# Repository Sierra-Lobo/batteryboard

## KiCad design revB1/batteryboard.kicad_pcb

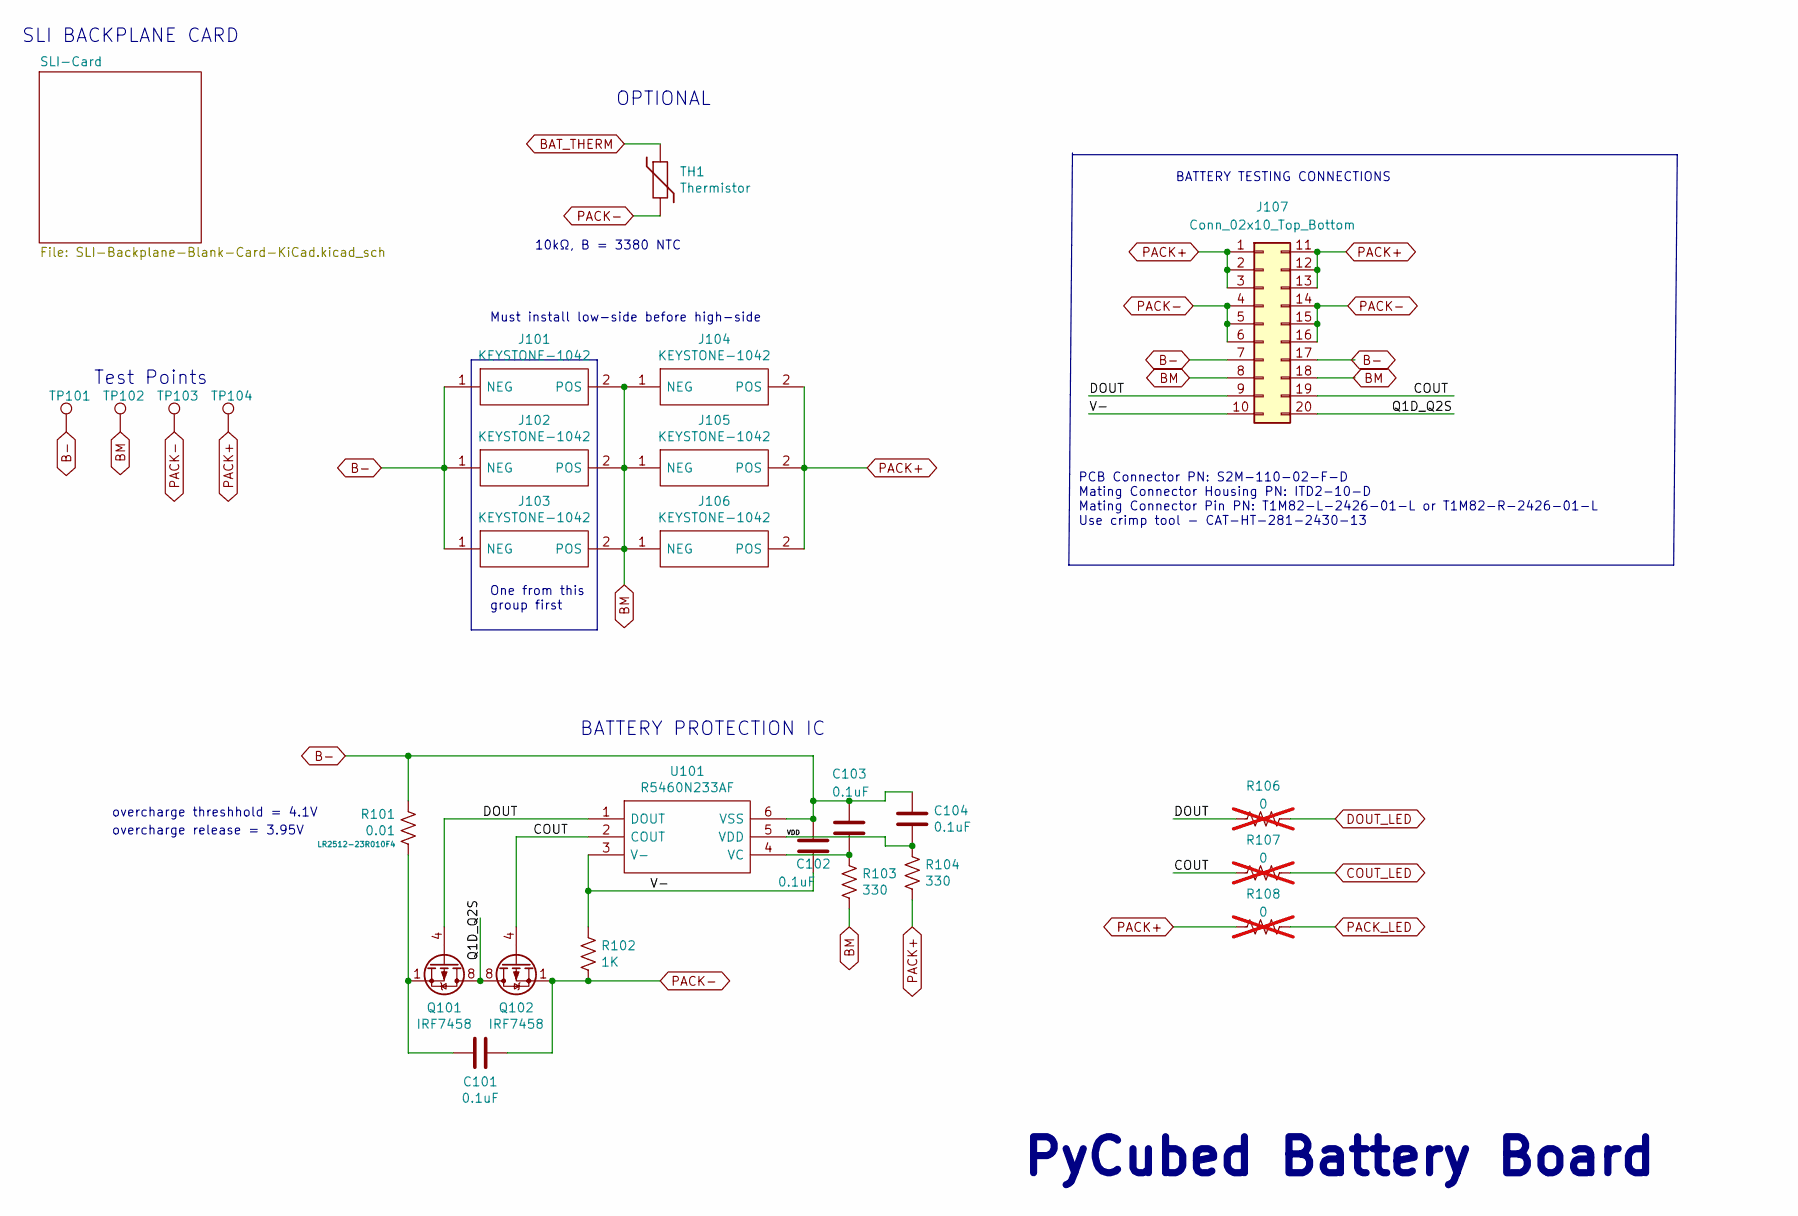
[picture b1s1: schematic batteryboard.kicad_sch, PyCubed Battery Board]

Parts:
C101, C102, C103, C104: 0.1uF; C_0603_1608Metric
J101: KEYSTONE-1042; KEYSTONE-1042_ALT_J1; Manufacturer_Part_Number 1042; Mouser Part Number 534-1042
J102, J104, J106: KEYSTONE-1042; Manufacturer_Part_Number 1042; Mouser Part Number 534-1042
J103: KEYSTONE-1042; KEYSTONE-1042_ALT_J5; Manufacturer_Part_Number 1042; Mouser Part Number 534-1042
J105: KEYSTONE-1042; KEYSTONE-1042_alt_J4; Manufacturer_Part_Number 1042; Mouser Part Number 534-1042
J107: Conn_02x10_Top_Bottom; SAMTEC_S2M-110-02-X-D
Q101, Q102: IRF7458; SOIC-8_3.9x4.9mm_P1.27mm; Manufacturer_Part_Number IRF7458
R101: 0.01; R_2512_6332Metric
R102: 1K; R_0603_1608Metric; Manufacturer_Part_Number LR2512-23R010F4
R103, R104: 330; R_0603_1608Metric
R106, R107, R108: 0; R_0603_1608Metric; not fitted
TH1: Thermistor; R_Axial_DIN0204_L3.6mm_D1.6mm_P5.08mm_Vertical
TP101, TP102, TP103, TP104: TestPoint; TestPoint_Loop_D1.80mm_Drill1.0mm_Beaded
U101: R5460N233AF; SOT95P280X130-6N; Manufacturer_Part_Number R5460N233AF-TR-FE; Mouser Part Number 848-R5460N233AFTRFE

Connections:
/COUT: J107.19, Q102.4 (G), R107.2, U101.2 (COUT)
/DOUT: J107.9, Q101.4 (G), R106.2, U101.1 (DOUT)
/Q1D_Q2S: J107.20, Q101.5 (D), Q101.6 (D), Q101.7 (D), Q101.8 (D), Q102.5 (D), Q102.6 (D), Q102.7 (D), Q102.8 (D)
/V-: C102.2, J107.10, R102.1, U101.3 (V-)
/VDD: C104.2, R104.2, U101.5 (VDD)
B-: C102.1, C103.1, C104.1, J101.1 (NEG), J102.1 (NEG), J103.1 (NEG), J107.7, J107.17, R101.1, TP101.1, U101.6 (VSS)
BAT_THERM: TH1.1; also elsewhere on the board
BM: J101.2 (POS), J102.2 (POS), J103.2 (POS), J104.1 (NEG), J105.1 (NEG), J106.1 (NEG), J107.8, J107.18, R103.1, TP102.1
COUT_LED: R107.1; also elsewhere on the board
DOUT_LED: R106.1; also elsewhere on the board
unnamed: C101.1, Q101.1 (S), Q101.2 (S), Q101.3 (S), R101.2
unnamed: C103.2, R103.2, U101.4 (VC)
PACK+: J104.2 (POS), J105.2 (POS), J106.2 (POS), J107.1, J107.2, J107.3, J107.11, J107.12, J107.13, R104.1, R108.2, TP104.1; also elsewhere on the board
PACK-: C101.2, J107.4, J107.5, J107.6, J107.14, J107.15, J107.16, Q102.1 (S), Q102.2 (S), Q102.3 (S), R102.2, TH1.2, TP103.1; also elsewhere on the board
PACK_LED: R108.1; also elsewhere on the board

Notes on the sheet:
overcharge release = 3.95V
Test Points
PCB Connector PN: S2M-110-02-F-D Mating Connector Housing PN: ITD2-10-D Mating Connector Pin PN: T1M82-L-2426-01-L or T1M82-R-2426-01-L Use crimp tool - CAT-HT-281-2430-13
Must install low-side before high-side
SLI BACKPLANE CARD
BATTERY TESTING CONNECTIONS
overcharge threshhold = 4.1V
OPTIONAL
BATTERY PROTECTION IC
One from this group first
PyCubed Battery Board
10kΩ, B = 3380 NTC

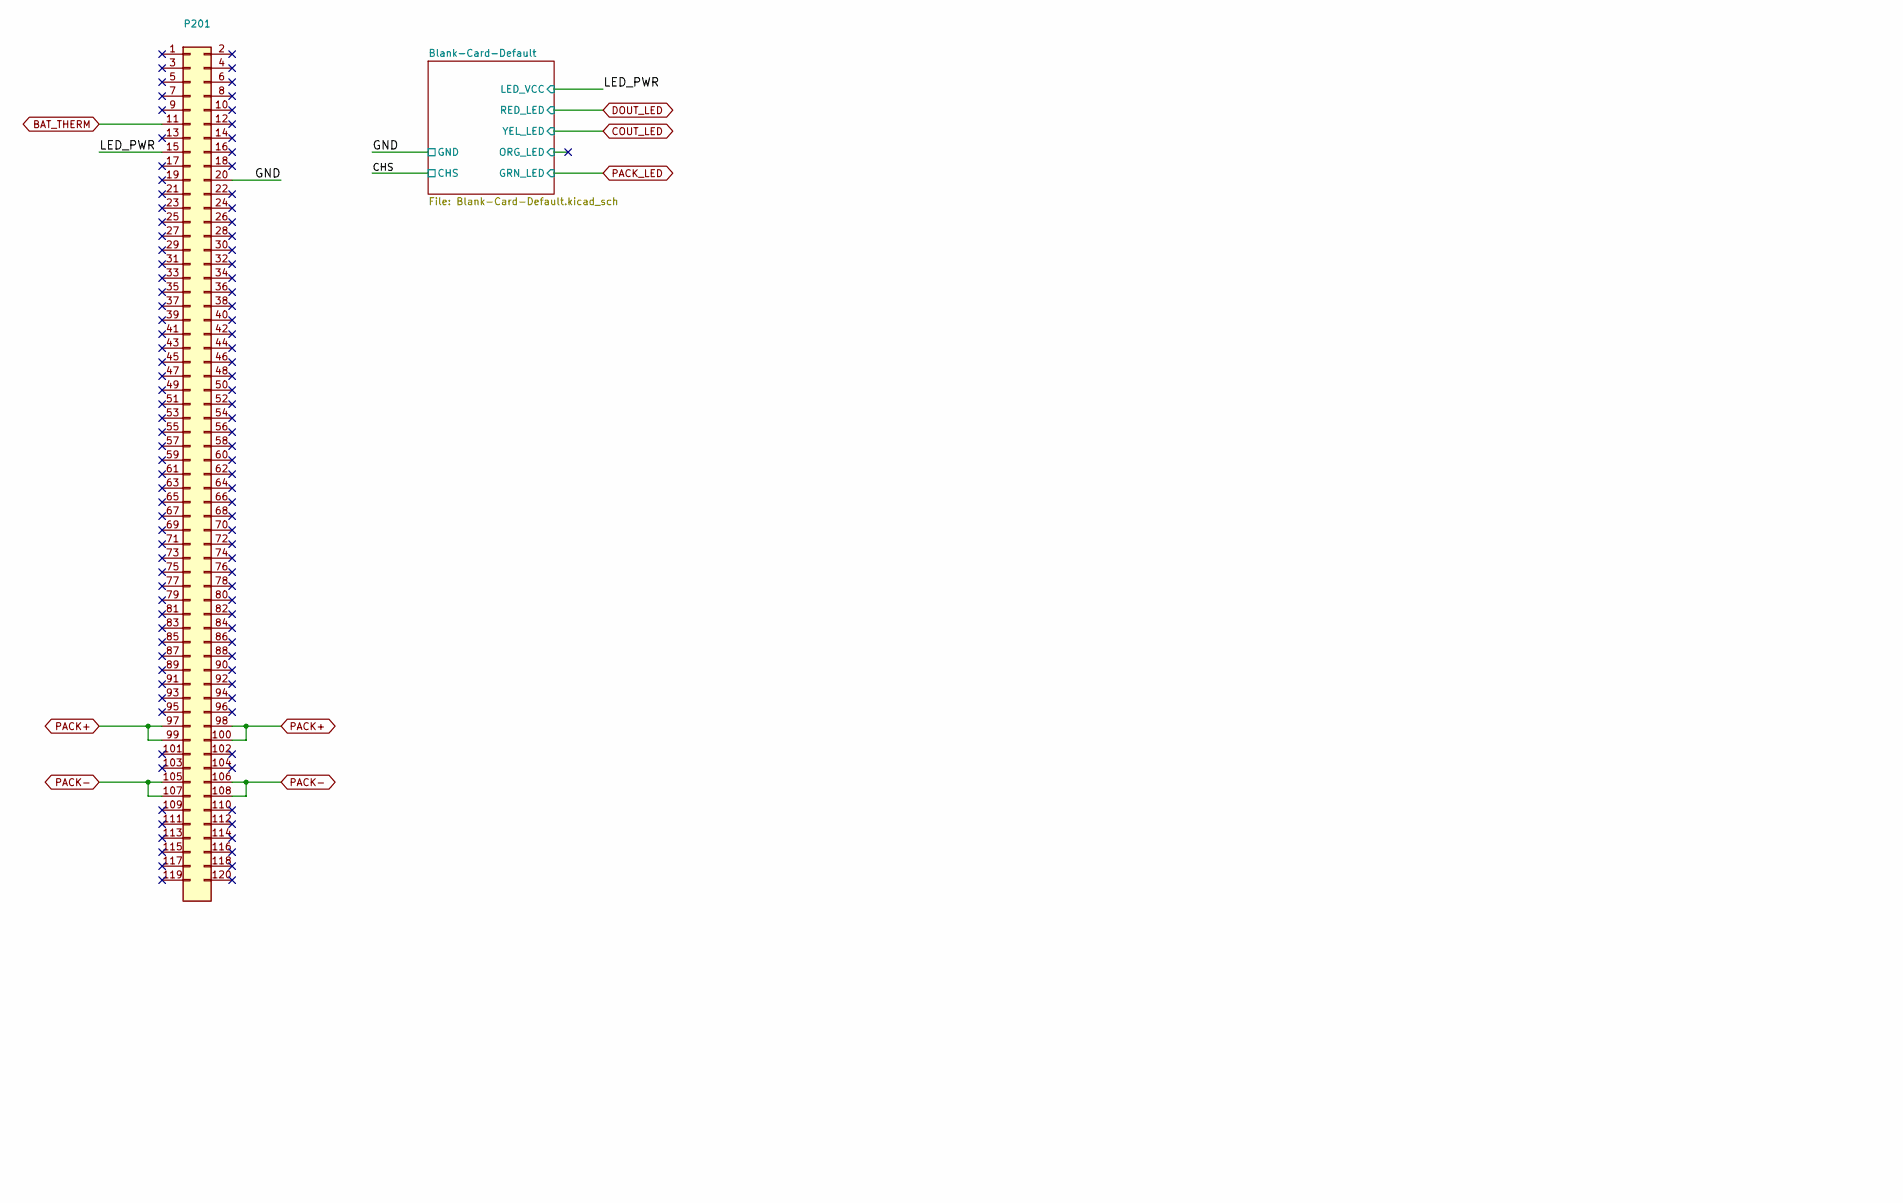
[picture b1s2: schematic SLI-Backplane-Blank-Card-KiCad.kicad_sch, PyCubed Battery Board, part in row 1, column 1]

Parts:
P201: Conn_02x60_Top_Bottom; HSEC8-160-CARD-EDGE

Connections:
/SLI-Card/GND: P201.20; also elsewhere on the board
/SLI-Card/LED_PWR: P201.15; also elsewhere on the board
BAT_THERM: P201.11; also elsewhere on the board
PACK+: P201.97, P201.98, P201.99, P201.100; also elsewhere on the board
PACK-: P201.105, P201.106, P201.107, P201.108; also elsewhere on the board

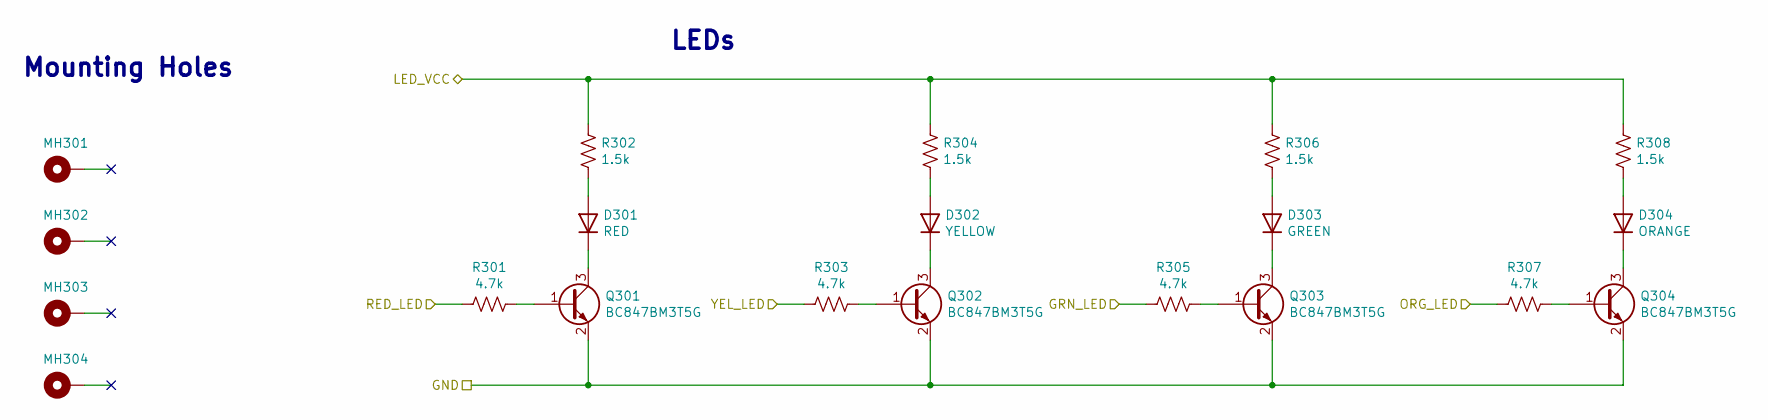
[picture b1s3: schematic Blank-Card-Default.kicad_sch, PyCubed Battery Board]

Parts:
D301: RED; APA2107x; Manufacturer_Part_Number APA2107LSECK/J3-PRV
D302: YELLOW; APA2107x; Manufacturer_Part_Number APA2107SYCK/J3-PRV
D303: GREEN; APA2107x; Manufacturer_Part_Number APA2107CGCK
D304: ORANGE; APA2107x; Manufacturer_Part_Number APA2107SECK/J4-PRV
MH301: MountingHole_Pad; 125mil_hole
MH302, MH303, MH304: SLI-Backplane-Blank-Card-KiCad:125mil_hole; 125mil_hole
Q301, Q302, Q303, Q304: BC847BM3T5G; SOT-723; Manufacturer_Part_Number BC847BM3T5G
R301, R303, R305, R307: 4.7k; R_0402_1005Metric
R302, R304, R306, R308: 1.5k; R_0402_1005Metric

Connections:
/SLI-Card/Blank-Card-Default/ORG_LED: R307.2
/SLI-Card/GND: Q301.2 (E), Q302.2 (E), Q303.2 (E), Q304.2 (E); also elsewhere on the board
/SLI-Card/LED_PWR: R302.1, R304.1, R306.1, R308.1; also elsewhere on the board
COUT_LED: R303.2; also elsewhere on the board
DOUT_LED: R301.2; also elsewhere on the board
unnamed: D301.2 (A), R302.2
unnamed: D301.1 (K), Q301.3 (C)
unnamed: D302.2 (A), R304.2
unnamed: D302.1 (K), Q302.3 (C)
unnamed: D303.2 (A), R306.2
unnamed: D303.1 (K), Q303.3 (C)
unnamed: D304.2 (A), R308.2
unnamed: D304.1 (K), Q304.3 (C)
unnamed: Q301.1 (B), R301.1
unnamed: Q302.1 (B), R303.1
unnamed: Q303.1 (B), R305.1
unnamed: Q304.1 (B), R307.1
PACK_LED: R305.2; also elsewhere on the board

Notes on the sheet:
Mounting Holes
LEDs

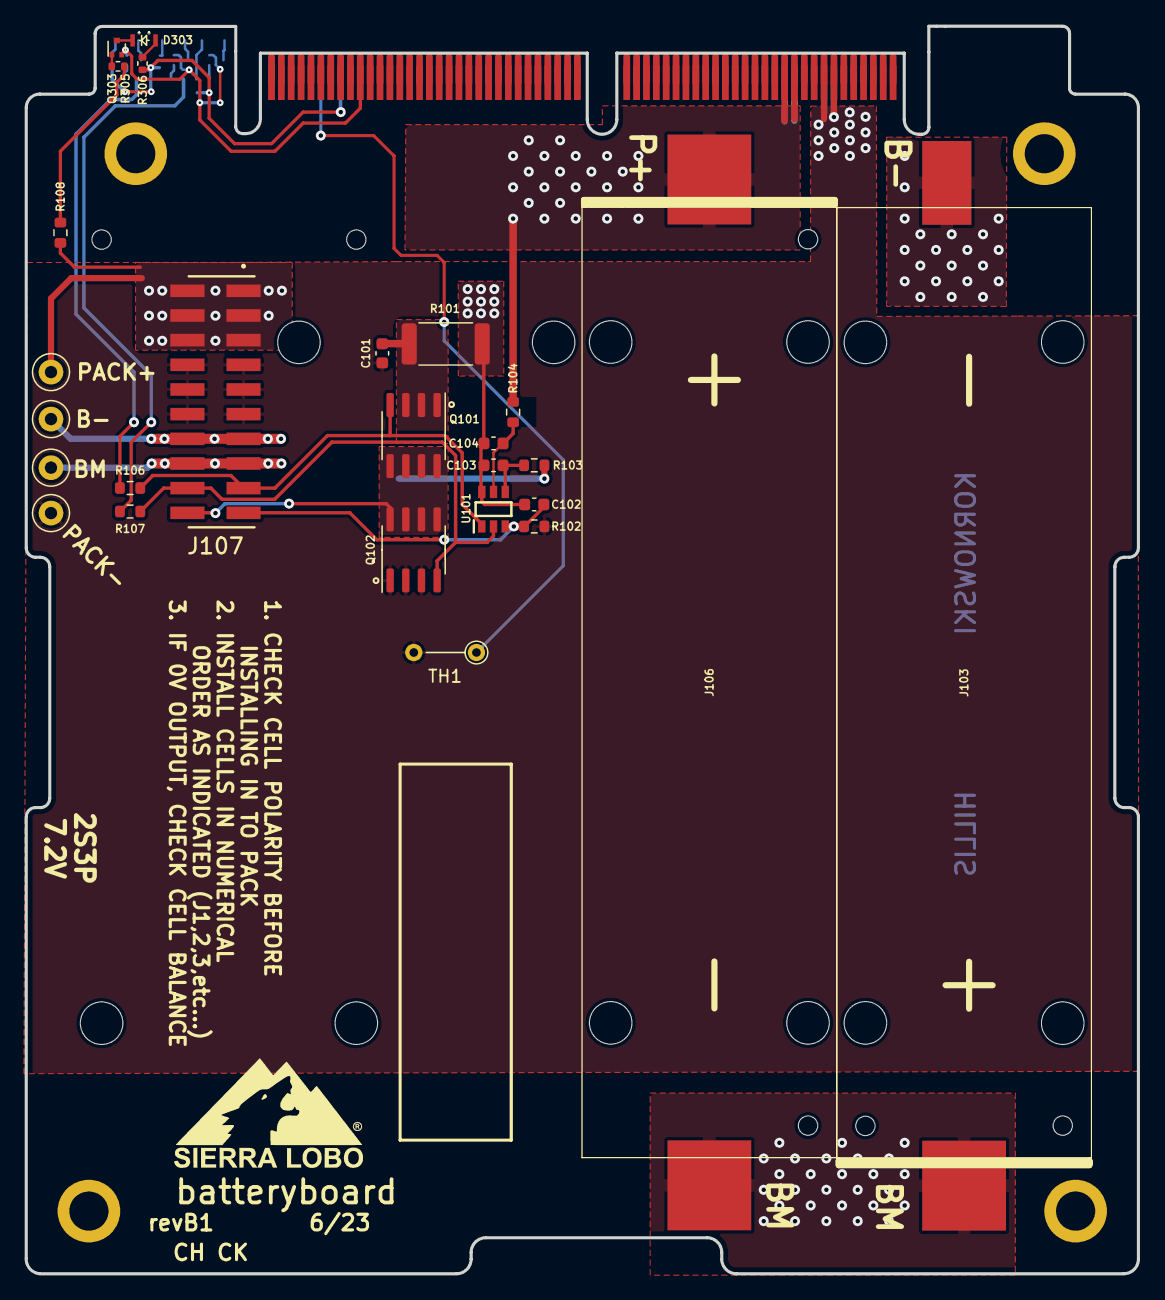
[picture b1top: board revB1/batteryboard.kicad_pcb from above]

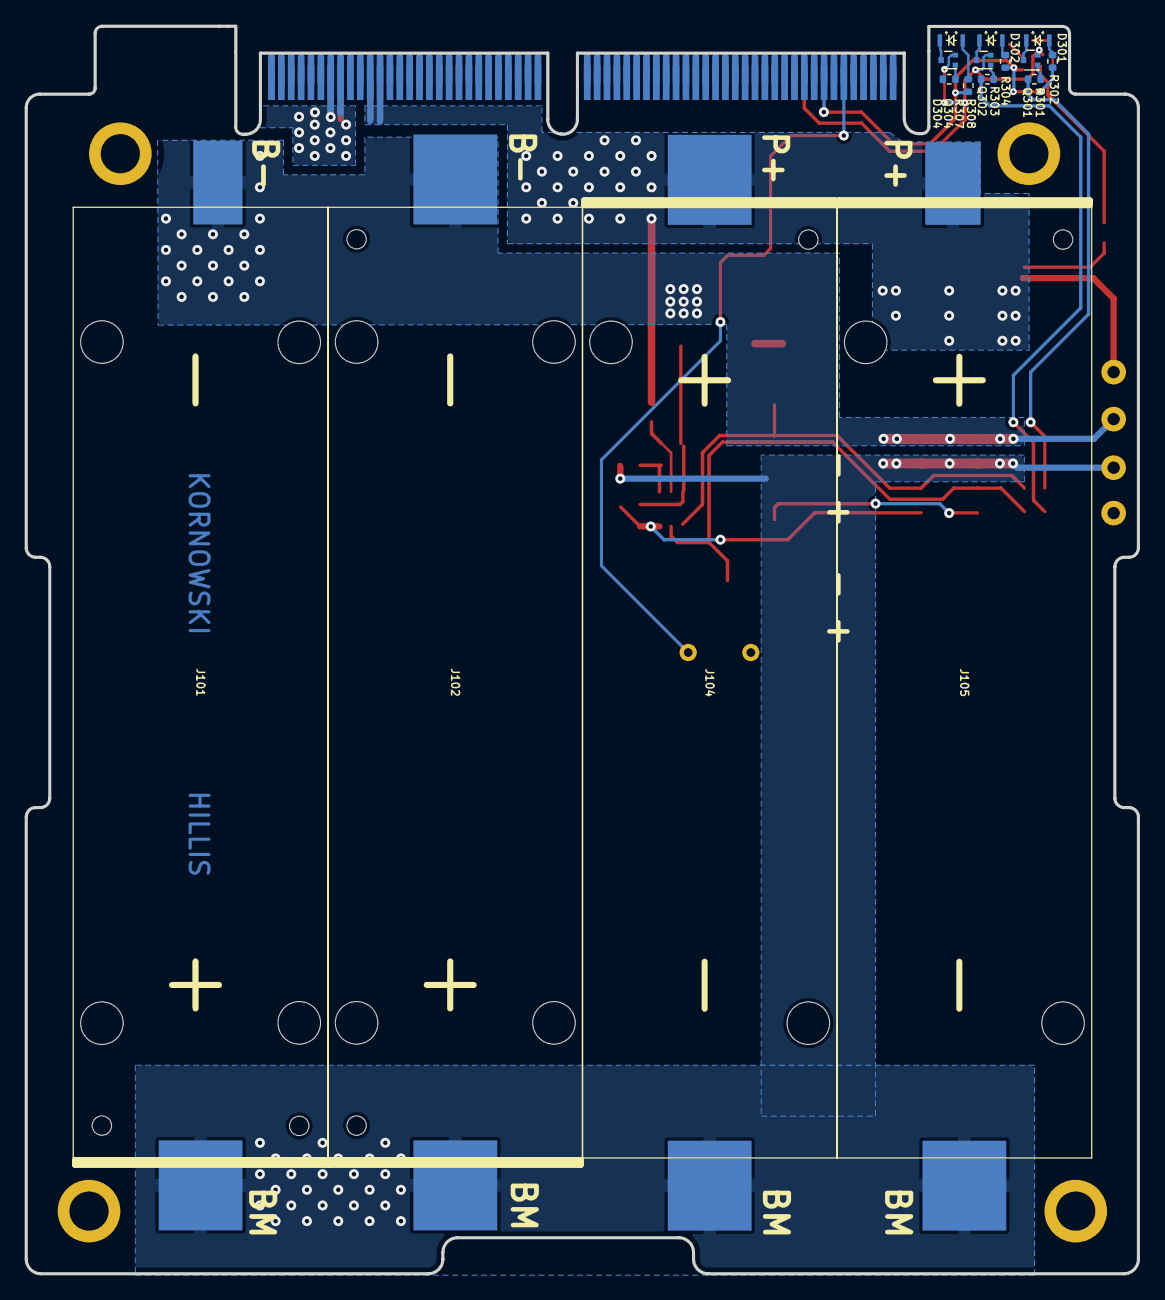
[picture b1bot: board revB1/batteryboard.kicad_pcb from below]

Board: 2 copper layers, 90.2 x 101.1 mm, 47 parts (16 on the bottom side), 29 nets.

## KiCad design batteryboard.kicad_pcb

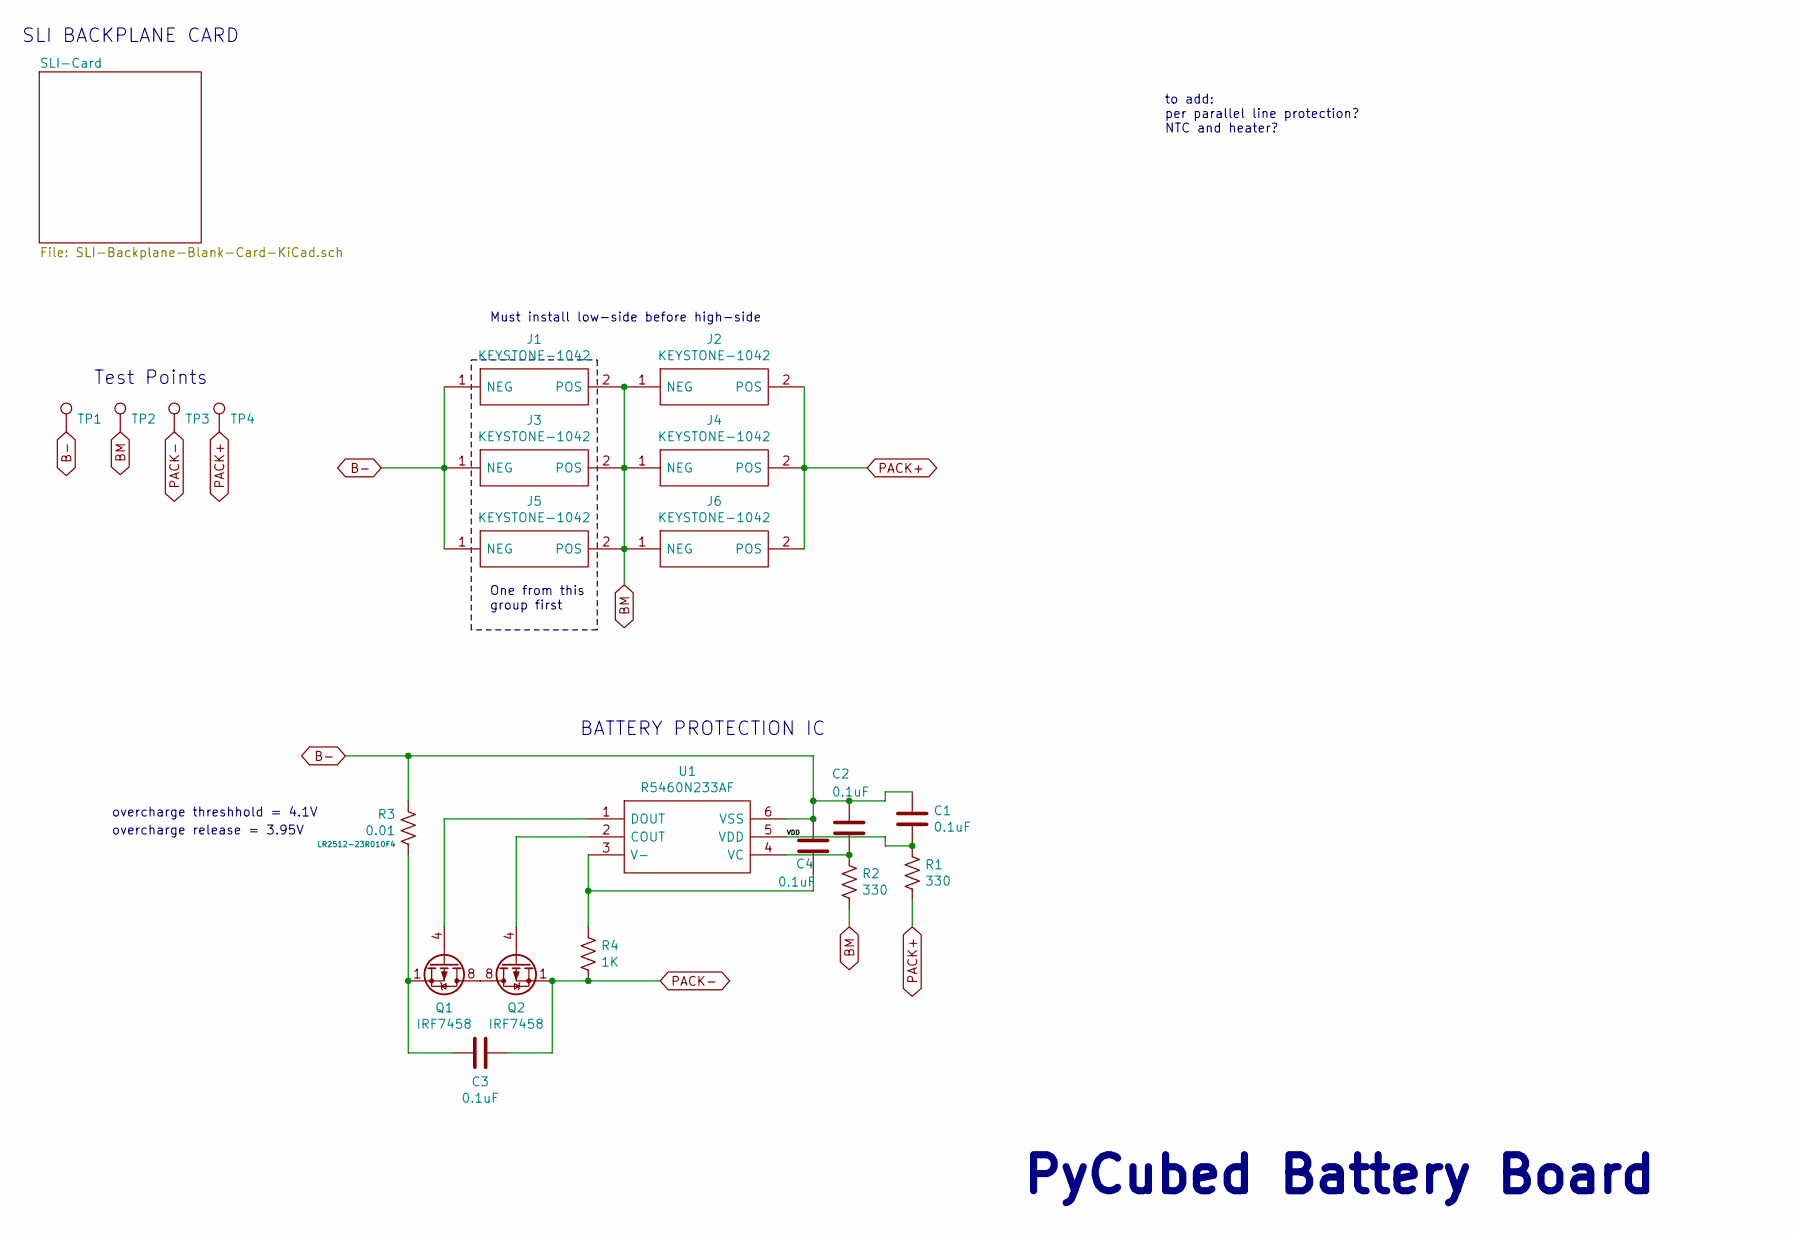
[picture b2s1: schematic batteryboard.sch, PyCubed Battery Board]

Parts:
C1, C2, C3, C4: 0.1uF; C_0603_1608Metric
J1: KEYSTONE-1042; KEYSTONE-1042_ALT_J1; Manufacturer_Part_Number 1042; Mouser Part Number 534-1042
J2, J3, J6: KEYSTONE-1042; Manufacturer_Part_Number 1042; Mouser Part Number 534-1042
J4: KEYSTONE-1042; KEYSTONE-1042_alt_J4; Manufacturer_Part_Number 1042; Mouser Part Number 534-1042
J5: KEYSTONE-1042; KEYSTONE-1042_ALT_J5; Manufacturer_Part_Number 1042; Mouser Part Number 534-1042
Q1, Q2: IRF7458; SOIC-8_3.9x4.9mm_P1.27mm; Manufacturer_Part_Number IRF7458
R1, R2: 330; R_0603_1608Metric
R3: 0.01; R_2512_6332Metric
R4: 1K; R_0603_1608Metric; Manufacturer_Part_Number LR2512-23R010F4
TP1, TP2, TP3, TP4: TestPoint; TestPoint_Loop_D1.80mm_Drill1.0mm_Beaded
U1: R5460N233AF; SOT95P280X130-6N; Manufacturer_Part_Number R5460N233AF-TR-FE; Mouser Part Number 848-R5460N233AFTRFE

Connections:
/VDD: C1.2, R1.2, U1.5 (VDD)
B-: C1.1, C2.1, C4.1, J1.1 (NEG), J3.1 (NEG), J5.1 (NEG), R3.1, TP1.1, U1.6 (VSS)
BM: J1.2 (POS), J2.1 (NEG), J3.2 (POS), J4.1 (NEG), J5.2 (POS), J6.1 (NEG), R2.1, TP2.1
unnamed: C2.2, R2.2, U1.4 (VC)
unnamed: C3.1, Q1.1 (S), Q1.2 (S), Q1.3 (S), R3.2
unnamed: C4.2, R4.1, U1.3 (V-)
unnamed: Q1.4 (G), U1.1 (DOUT)
unnamed: Q1.5 (D), Q1.6 (D), Q1.7 (D), Q1.8 (D), Q2.5 (D), Q2.6 (D), Q2.7 (D), Q2.8 (D)
unnamed: Q2.4 (G), U1.2 (COUT)
PACK+: J2.2 (POS), J4.2 (POS), J6.2 (POS), R1.1, TP4.1; also elsewhere on the board
PACK-: C3.2, Q2.1 (S), Q2.2 (S), Q2.3 (S), R4.2, TP3.1; also elsewhere on the board

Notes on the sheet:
Must install low-side before high-side
One from this group first
Test Points
BATTERY PROTECTION IC
PyCubed Battery Board
SLI BACKPLANE CARD
overcharge threshhold = 4.1V
overcharge release = 3.95V
to add: per parallel line protection? NTC and heater?

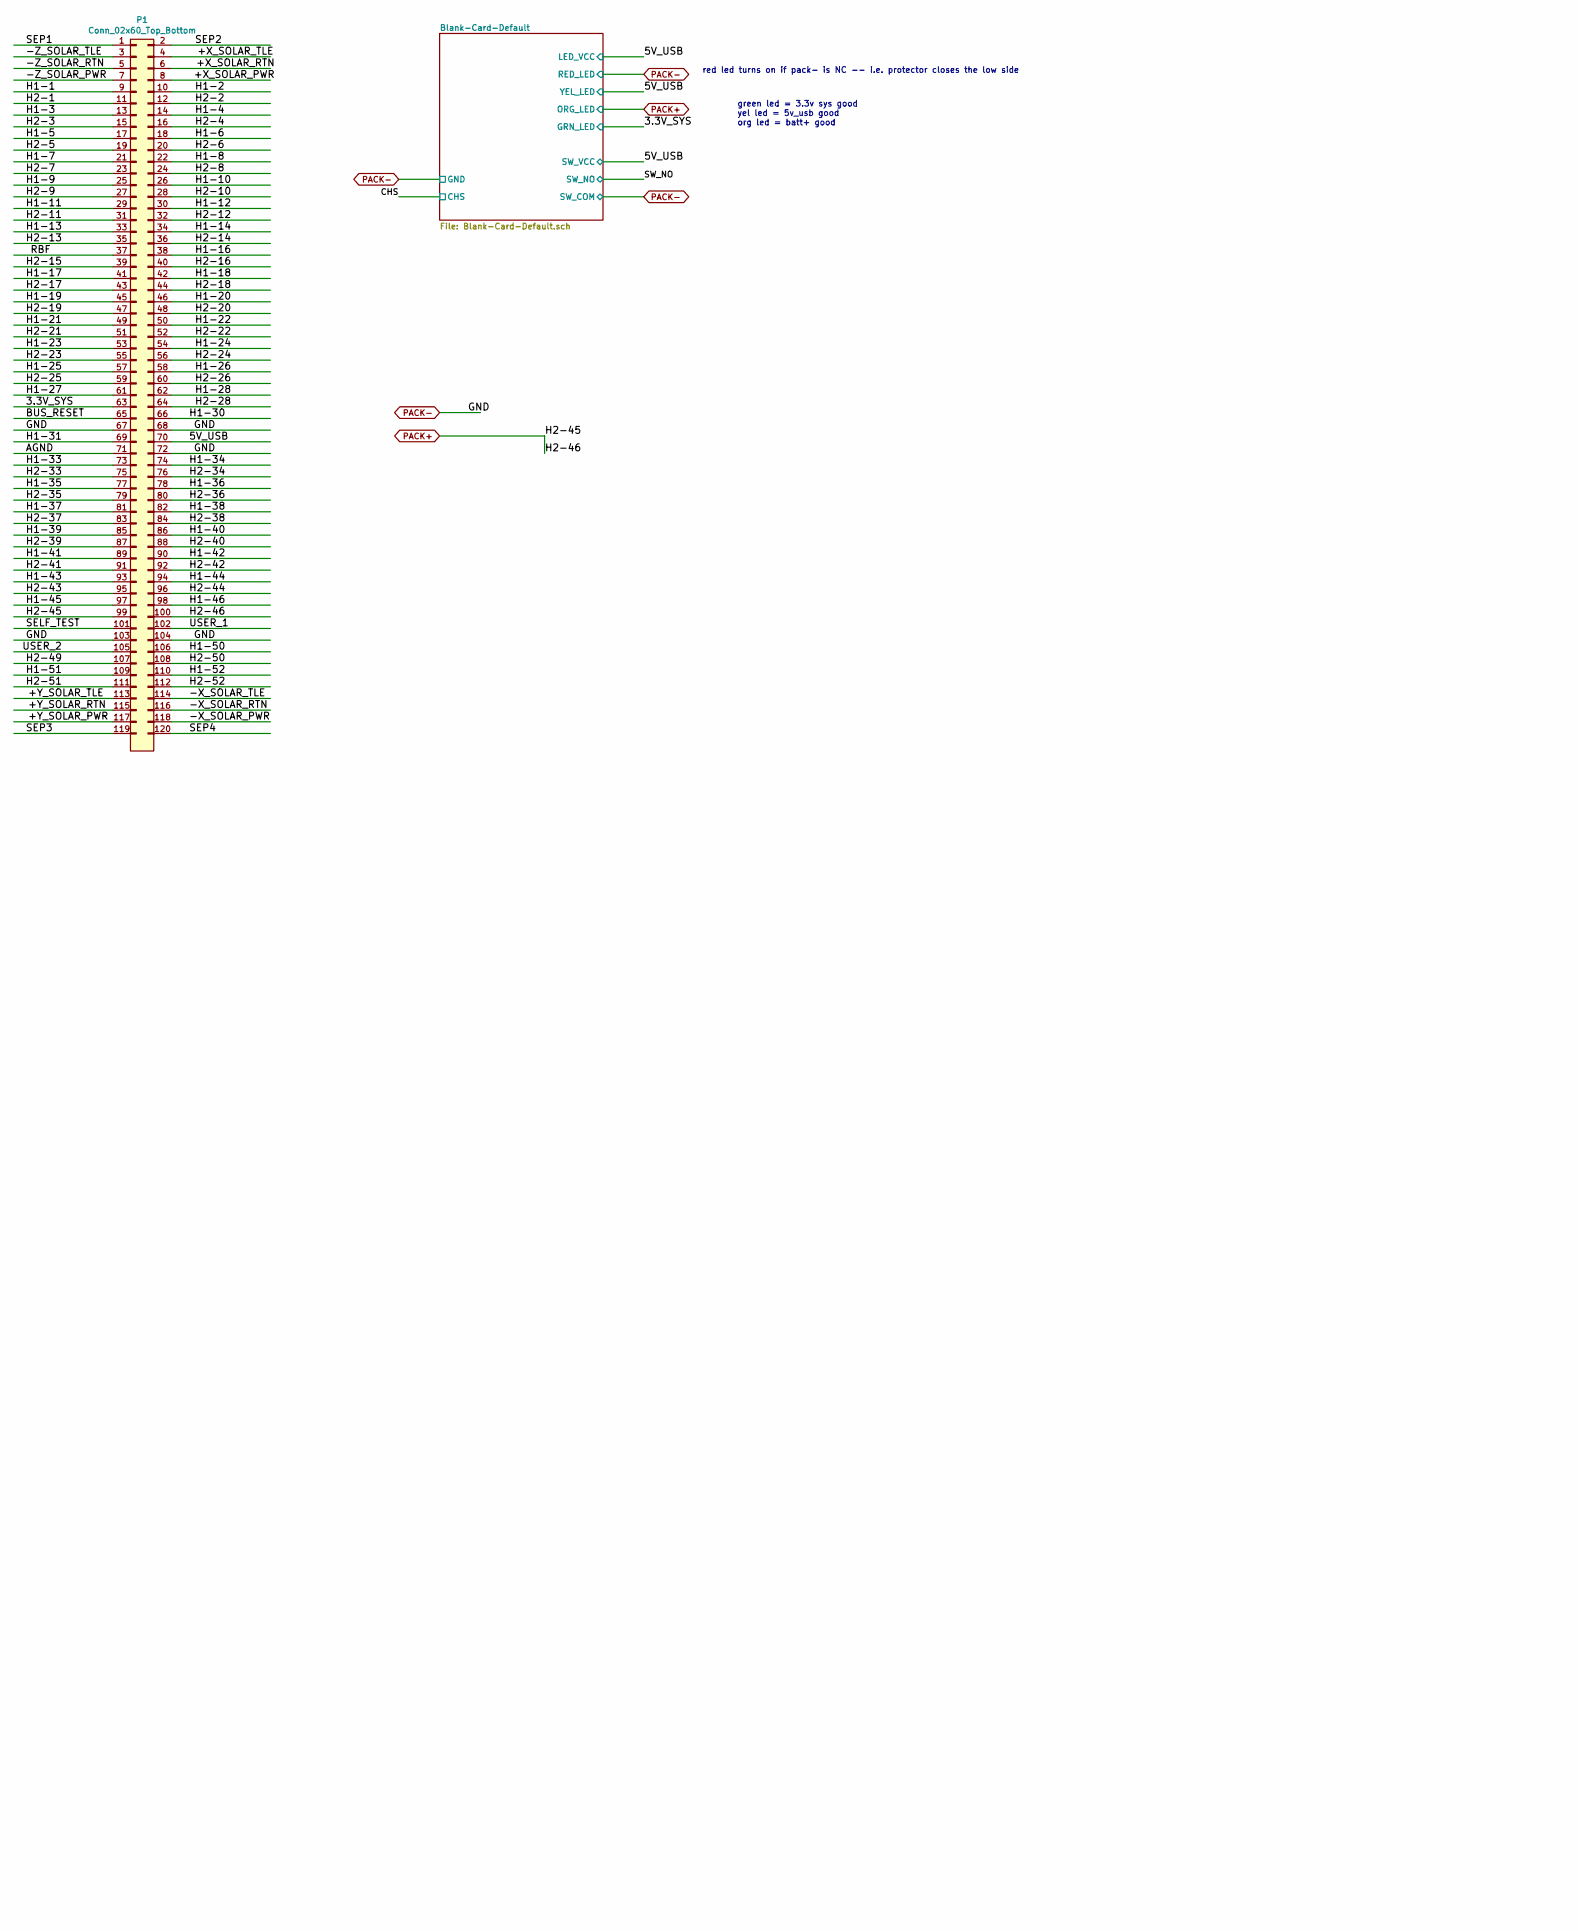
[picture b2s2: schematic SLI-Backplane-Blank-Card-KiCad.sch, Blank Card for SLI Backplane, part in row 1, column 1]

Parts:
P1: Conn_02x60_Top_Bottom; HSEC8-160-CARD-EDGE

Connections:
/SLI-Card/3.3V_SYS: P1.63; also elsewhere on the board
/SLI-Card/5V_USB: P1.70; also elsewhere on the board
/SLI-Card/+X_SOLAR_PWR: P1.8
/SLI-Card/+X_SOLAR_RTN: P1.6
/SLI-Card/+X_SOLAR_TLE: P1.4
/SLI-Card/+Y_SOLAR_PWR: P1.117
/SLI-Card/+Y_SOLAR_RTN: P1.115
/SLI-Card/+Y_SOLAR_TLE: P1.113
/SLI-Card/-X_SOLAR_PWR: P1.118
/SLI-Card/-X_SOLAR_RTN: P1.116
/SLI-Card/-X_SOLAR_TLE: P1.114
/SLI-Card/-Z_SOLAR_PWR: P1.7
/SLI-Card/-Z_SOLAR_RTN: P1.5
/SLI-Card/-Z_SOLAR_TLE: P1.3
/SLI-Card/AGND: P1.71
/SLI-Card/BUS_RESET: P1.65
/SLI-Card/H1-1: P1.9
/SLI-Card/H1-2: P1.10
/SLI-Card/H1-3: P1.13
/SLI-Card/H1-4: P1.14
/SLI-Card/H1-5: P1.17
/SLI-Card/H1-6: P1.18
/SLI-Card/H1-7: P1.21
/SLI-Card/H1-8: P1.22
/SLI-Card/H1-9: P1.25
/SLI-Card/H1-10: P1.26
/SLI-Card/H1-11: P1.29
/SLI-Card/H1-12: P1.30
/SLI-Card/H1-13: P1.33
/SLI-Card/H1-14: P1.34
/SLI-Card/H1-16: P1.38
/SLI-Card/H1-17: P1.41
/SLI-Card/H1-18: P1.42
/SLI-Card/H1-19: P1.45
/SLI-Card/H1-20: P1.46
/SLI-Card/H1-21: P1.49
/SLI-Card/H1-22: P1.50
/SLI-Card/H1-23: P1.53
/SLI-Card/H1-24: P1.54
/SLI-Card/H1-25: P1.57
/SLI-Card/H1-26: P1.58
/SLI-Card/H1-27: P1.61
/SLI-Card/H1-28: P1.62
/SLI-Card/H1-30: P1.66
/SLI-Card/H1-31: P1.69
/SLI-Card/H1-33: P1.73
/SLI-Card/H1-34: P1.74
/SLI-Card/H1-35: P1.77
/SLI-Card/H1-36: P1.78
/SLI-Card/H1-37: P1.81
/SLI-Card/H1-38: P1.82
/SLI-Card/H1-39: P1.85
/SLI-Card/H1-40: P1.86
/SLI-Card/H1-41: P1.89
/SLI-Card/H1-42: P1.90
/SLI-Card/H1-43: P1.93 (Pin93)
/SLI-Card/H1-44: P1.94
/SLI-Card/H1-45: P1.97
/SLI-Card/H1-46: P1.98
/SLI-Card/H1-50: P1.106
/SLI-Card/H1-51: P1.109
/SLI-Card/H1-52: P1.110
/SLI-Card/H2-1: P1.11
/SLI-Card/H2-2: P1.12
/SLI-Card/H2-3: P1.15
/SLI-Card/H2-4: P1.16
/SLI-Card/H2-5: P1.19
/SLI-Card/H2-6: P1.20
/SLI-Card/H2-7: P1.23
/SLI-Card/H2-8: P1.24
/SLI-Card/H2-9: P1.27
/SLI-Card/H2-10: P1.28
/SLI-Card/H2-11: P1.31
/SLI-Card/H2-12: P1.32
/SLI-Card/H2-13: P1.35
/SLI-Card/H2-14: P1.36
/SLI-Card/H2-15: P1.39
/SLI-Card/H2-16: P1.40
/SLI-Card/H2-17: P1.43
/SLI-Card/H2-18: P1.44
/SLI-Card/H2-19: P1.47
/SLI-Card/H2-20: P1.48
/SLI-Card/H2-21: P1.51
/SLI-Card/H2-22: P1.52
/SLI-Card/H2-23: P1.55
/SLI-Card/H2-24: P1.56
/SLI-Card/H2-25: P1.59
/SLI-Card/H2-26: P1.60
/SLI-Card/H2-28: P1.64
/SLI-Card/H2-33: P1.75
/SLI-Card/H2-34: P1.76
/SLI-Card/H2-35: P1.79
/SLI-Card/H2-36: P1.80
/SLI-Card/H2-37: P1.83
/SLI-Card/H2-38: P1.84
/SLI-Card/H2-39: P1.87
/SLI-Card/H2-40: P1.88
/SLI-Card/H2-41: P1.91
/SLI-Card/H2-42: P1.92
/SLI-Card/H2-43: P1.95
/SLI-Card/H2-44: P1.96
/SLI-Card/H2-49: P1.107
/SLI-Card/H2-50: P1.108
/SLI-Card/H2-51: P1.111
/SLI-Card/H2-52: P1.112
/SLI-Card/RBF: P1.37
/SLI-Card/SELF_TEST: P1.101
/SLI-Card/SEP1: P1.1
/SLI-Card/SEP2: P1.2
/SLI-Card/SEP3: P1.119
/SLI-Card/SEP4: P1.120
/SLI-Card/USER_1: P1.102
/SLI-Card/USER_2: P1.105
PACK+: P1.99, P1.100; also elsewhere on the board
PACK-: P1.67, P1.68, P1.72, P1.103, P1.104; also elsewhere on the board

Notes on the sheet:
green led = 3.3v sys good yel led = 5v_usb good org led = batt+ good
red led turns on if pack- is NC -- i.e. protector closes the low side

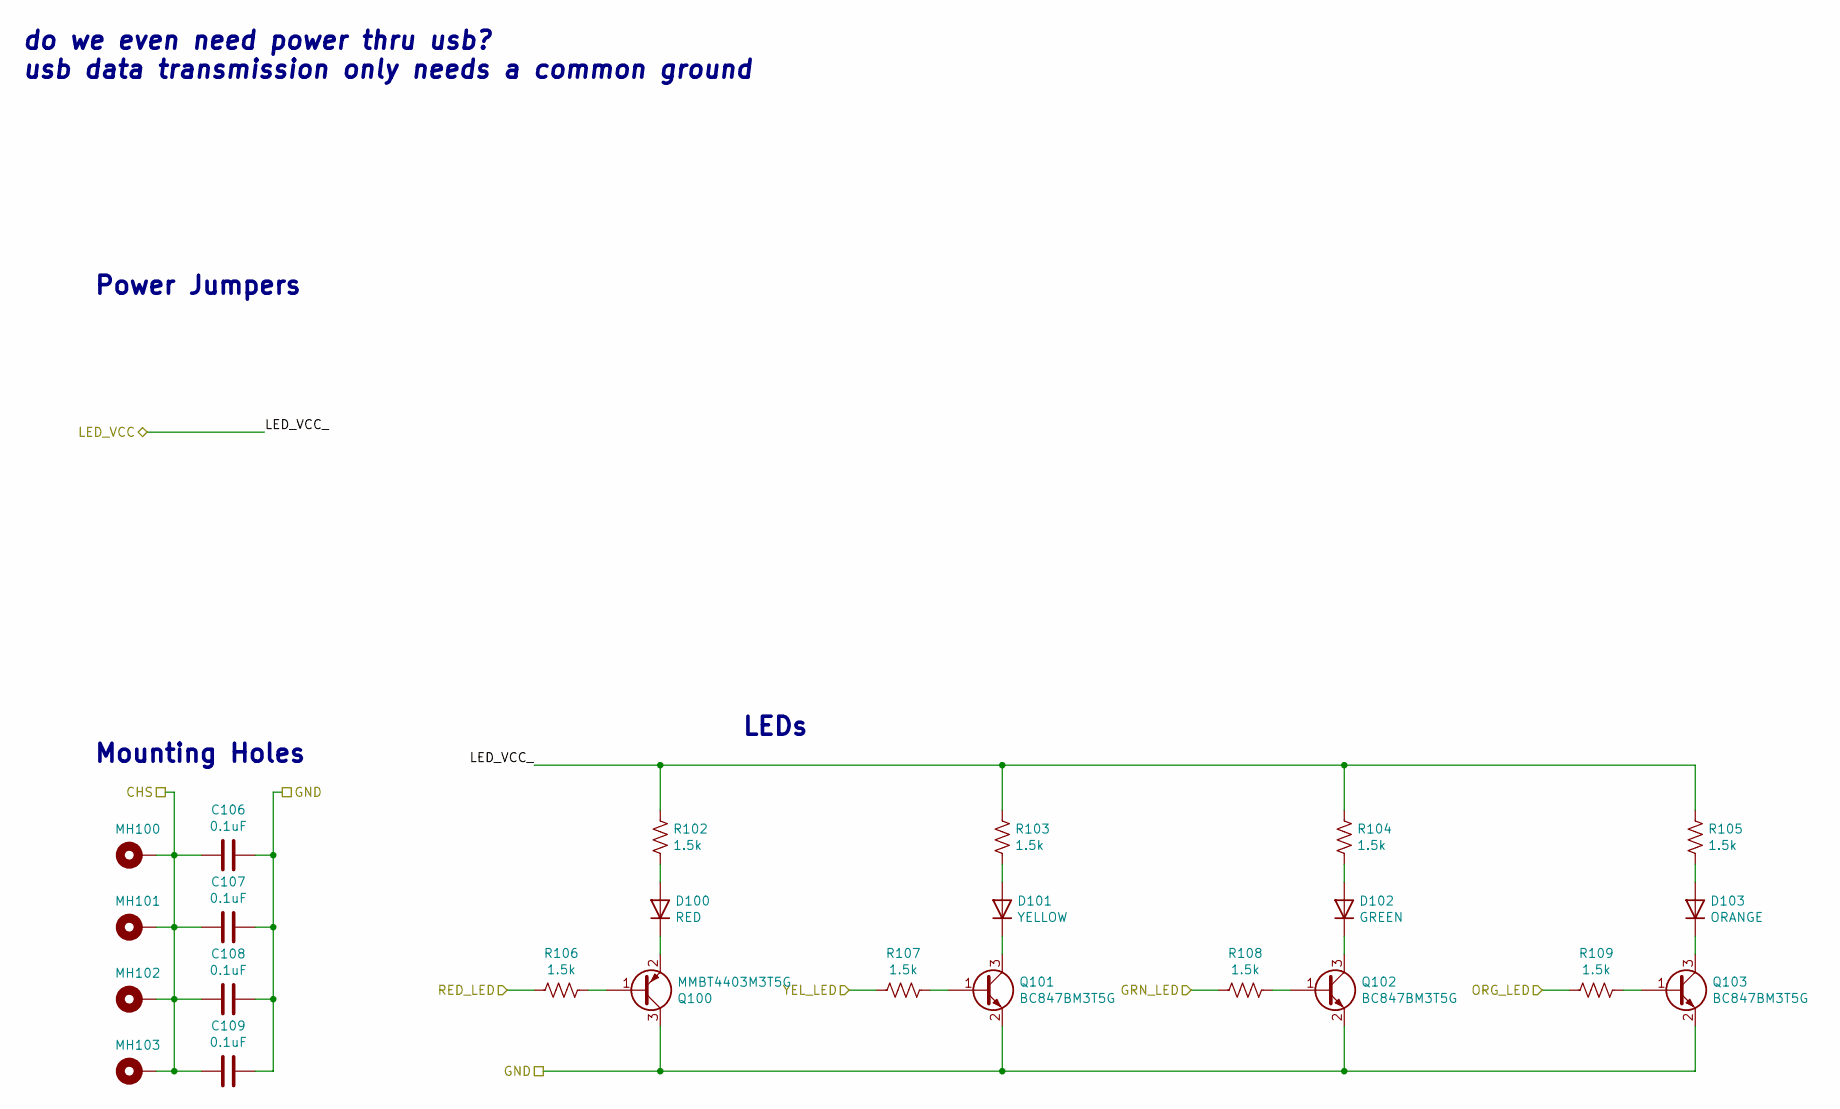
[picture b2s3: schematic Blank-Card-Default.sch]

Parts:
C106, C107, C108, C109: 0.1uF; C_0402_1005Metric
D100: RED; APA2107x; Manufacturer_Part_Number APA2107LSECK/J3-PRV
D101: YELLOW; APA2107x; Manufacturer_Part_Number APA2107SYCK/J3-PRV
D102: GREEN; APA2107x; Manufacturer_Part_Number APA2107CGCK
D103: ORANGE; APA2107x; Manufacturer_Part_Number APA2107SECK/J4-PRV
MH100: MountingHole_Pad; 125mil_hole
MH101, MH102, MH103: SLI-Backplane-Blank-Card-KiCad:125mil_hole; 125mil_hole
Q100: MMBT4403M3T5G; SOT-723; Manufacturer_Part_Number MMBT4403M3T5G
Q101, Q102, Q103: BC847BM3T5G; SOT-723; Manufacturer_Part_Number BC847BM3T5G
R102, R103, R104, R105, R106, R107, R108, R109: 1.5k; R_0402_1005Metric

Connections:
/SLI-Card/3.3V_SYS: R108.2; also elsewhere on the board
/SLI-Card/5V_USB: R102.1, R103.1, R104.1, R105.1, R107.2; also elsewhere on the board
/SLI-Card/CHS: C106.2, C107.2, C108.2, C109.2, MH100.1, MH101.1, MH102.1, MH103.1
unnamed: D100.1 (K), Q100.2 (E)
unnamed: D100.2 (A), R102.2
unnamed: D101.1 (K), Q101.3 (C)
unnamed: D101.2 (A), R103.2
unnamed: D102.1 (K), Q102.3 (C)
unnamed: D102.2 (A), R104.2
unnamed: D103.1 (K), Q103.3 (C)
unnamed: D103.2 (A), R105.2
unnamed: Q100.1 (B), R106.1
unnamed: Q101.1 (B), R107.1
unnamed: Q102.1 (B), R108.1
unnamed: Q103.1 (B), R109.1
PACK+: R109.2; also elsewhere on the board
PACK-: C106.1, C107.1, C108.1, C109.1, Q100.3 (C), Q101.2 (E), Q102.2 (E), Q103.2 (E), R106.2; also elsewhere on the board

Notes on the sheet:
LEDs
do we even need power thru usb? usb data transmission only needs a common ground
Mounting Holes
Power Jumpers
